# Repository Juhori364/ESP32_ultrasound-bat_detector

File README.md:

# ESP32_ultrasound-bat_detector

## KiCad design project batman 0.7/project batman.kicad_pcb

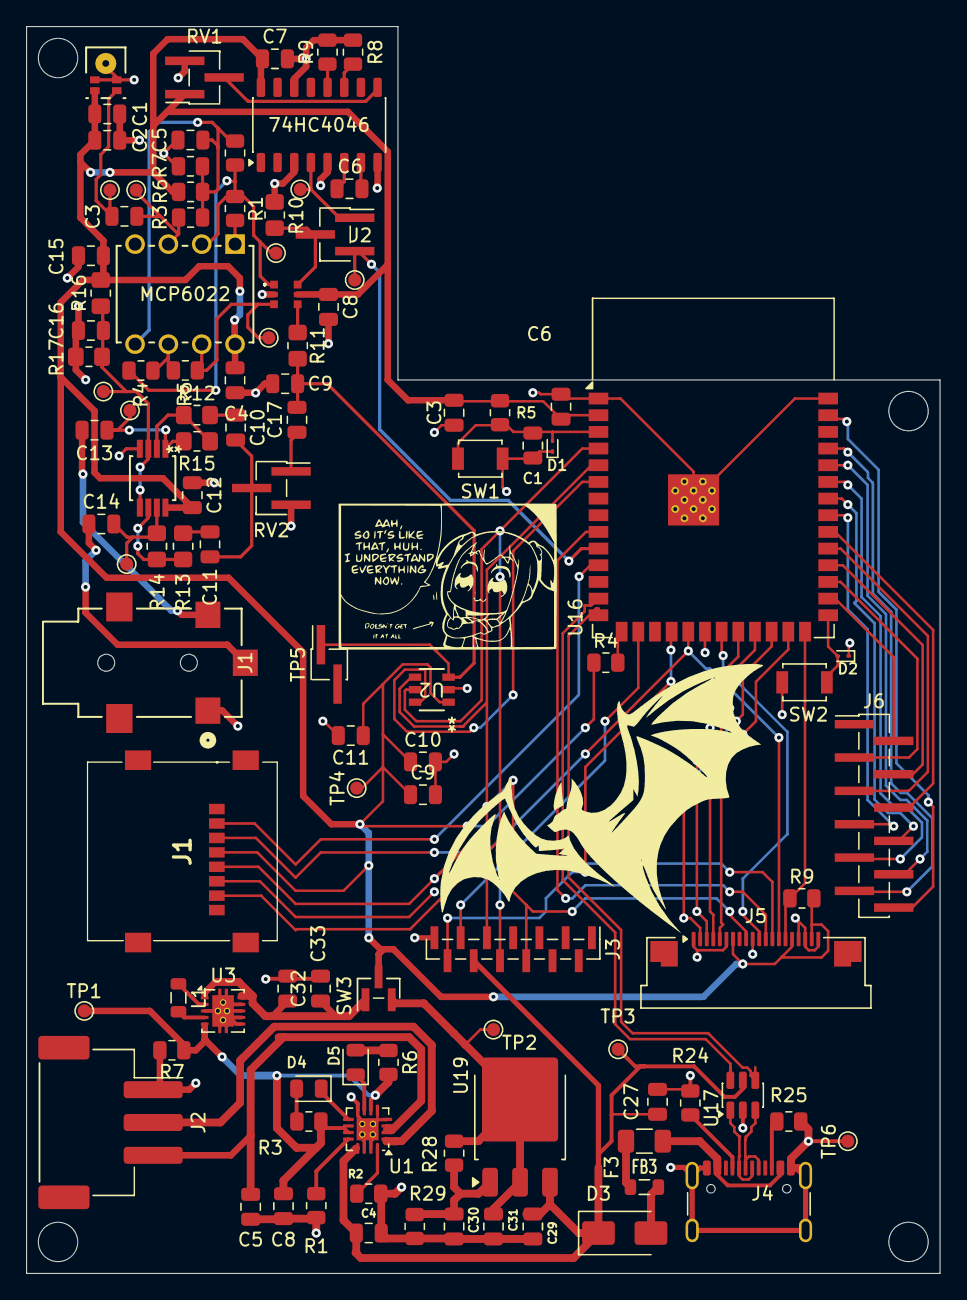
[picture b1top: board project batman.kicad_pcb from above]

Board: 2 copper layers, 69.6 x 95.0 mm, 109 parts (0 on the bottom side), 82 nets.

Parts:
74HC4046: 4046; JEITA_SOIC-16_3.9x9.9mm_P1.27mm
74LVC1G3156GW1: 74LVC1G3157GW125
C1: 1u; C_0805_2012Metric
C1#2, C15, C16, C17: 1uF; C_0805_2012Metric
C2: 1000pF; C_0805_2012Metric
C3: 150pF; C_0805_2012Metric
C3#2, C27: 100n; C_0805_2012Metric
C4, C7, C8, C9#2, C12: 100nF; C_0805_2012Metric
C4#2: 1µF; C_0805_2012Metric
C5, C29, C30: 10uF; C_0805_2012Metric
C5#2, C8#2, C9, C10#2, C11: 4.7µF; C_0805_2012Metric
C6: 0; C_0805_2012Metric
C6#2: 10u; C_0805_2012Metric
C10, C11#2: 2.2uF; C_0805_2012Metric
C13, C14: 220uF; C_0805_2012Metric
C31, C32, C33: 100uF; C_0805_2012Metric
D1, D2: ESD9B3.3ST5G; D_SOD-923
D3: B140-E3; D_SMA
D4, D5: LED; LED_0805_2012Metric
F3: 1A; Fuse_1206_3216Metric
FB3: BLM21PG220; L_0805_2012Metric
G: LOGO
IMP23ABSU1: RHLGA5_3P5X2P65X0P98_STM
J1: MEM2067-02-180-00-A; MEM20670218000A
J1#2: AudioJack2_Ground; JACK_1503 03_LMB
J2: Conn_01x03; JST_XH_S3B-XH-SM4-TB_1x03-1MP_P2.50mm_Horizontal
J2#2: Conn_01x03_Pin; PinHeader_1x03_P1.27mm_Vertical_SMD_Pin1Right
J3: Conn_01x13_Pin; PinHeader_1x13_P1.00mm_Vertical_SMD_Pin1Left
J4: USB_C_Receptacle_USB2.0_16P; USB_C_Receptacle_GCT_USB4105-xx-A_16P_TopMnt_Horizontal
J5: Conn_01x20_Pin; Amphenol_F32Q-1A7x1-11020_1x20-1MP_P0.5mm_Horizontal
J6: Conn_01x12_Pin; PinHeader_1x12_P1.27mm_Vertical_SMD_Pin1Left
L1: 2.2µH; L_0805_2012Metric
MCP6022: PDIP8_300MC_MCH
R1: 4.32k; R_0805_2012Metric
R1#2, R7: 100k; R_0805_2012Metric
R2: 2.94k; R_0805_2012Metric
R2#2, R4, R4#2, R5, R5#2, R6#2, R7#2, R9: 10k; R_0805_2012Metric
R3: 50k; R_0805_2012Metric
R3#2, R6: 1k; R_0805_2012Metric
R8, R9#2: 0; R_0805_2012Metric
R10, R16, R17: 100k; R_0805_2012Metric_Pad1.20x1.40mm_HandSolder
R11: 330; R_0805_2012Metric_Pad1.20x1.40mm_HandSolder
R12, R13: 3.9k; R_0805_2012Metric_Pad1.20x1.40mm_HandSolder
R14, R15: 39k; R_0805_2012Metric_Pad1.20x1.40mm_HandSolder
R24, R25: 5.1k; R_0805_2012Metric
R28: 610; R_0805_2012Metric
R29: 1000; R_0805_2012Metric
RV1, RV2: POT; PinHeader_1x03_P1.27mm_Vertical_SMD_Pin1Right
SW1: RESET; SW_SPST_B3U-1000P
SW2: BOOT; SW_SPST_B3U-1000P
SW3: SW_Nidec_CAS-120A1; PinHeader_1x03_P1.00mm_Vertical_SMD_Pin1Left
TP1, TP1#2, TP2, TP2#2, TP3, TP4, TP4#2, TP5#2, TP6, TP7, TP8, TP9, TP10, TP11: TestPoint; TestPoint_Pad_D1.0mm
TP5: TestPoint; PinHeader_1x02_P1.27mm_Vertical_SMD_Pin1Right
TS482IST1: MINISO8_3P1X3P2X0P65_STM
U1: BQ24230RGT; VQFN-16-1EP_3x3mm_P0.5mm_EP1.68x1.68mm_ThermalVias
U2: AD7276AUJZ-500RL7; UJ_6_ADI
U3: TPS63001; Texas_DRC0010J_ThermalVias
U16: ESP32-S3-WROOM-1
U17: USBLC6-2SC6; SOT-23-6
U19: LM1117DT-ADJ; TO-252-3_TabPin2

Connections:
+3.3V: 74HC4046.16 (VDD), 74LVC1G3156GW1.5 (Vcc), C1#2.2, C2.2, C3#2.1, C4.2, C6#2.1, C7.1, C8.1, C9.1, C10#2.1, C11.1, C12.2, C15.1, IMP23ABSU1.5 (Vin), J1.P4 (VDD), J5.7, J5.16, J5.19, MCP6022.8 (Vdd), R4.1, R5#2.1, R6#2.2, R9.2, R16.2, RV1.1, SW3.2 (B), TP4#2.1 (1_1), TS482IST1.8 (VCC), U2.1 (VDD), U16.2 (3V3)
+5V: C4#2.1, C27.1, C29.1, D3.1 (K), J3.10, TP3.1 (1_1), U1.13 (IN), U17.5 (VBUS), U19.3 (VI)
/ADC_CS: U2.6 (CS*), U16.6 (IO6)
/D+: J4.A6 (D+), J4.B6 (D+), U17.3 (I/O2)
/D-: J4.A7 (D-), J4.B7 (D-), U17.1 (I/O1)
/DP2_CS: J5.12, U16.9 (IO16)
/DP_CS: J3.12, U16.18 (IO10)
/DP_RESET: J3.11, U16.16 (IO46)
/DP_RESET2: J5.15, R9.1, U16.26 (IO45)
/DP_cmd_select: J5.11, U16.21 (IO13)
/EN: C1.1, D1.2 (A2), R5#2.2, SW1.2 (B), U16.3 (EN)
/ESP LO: J2#2.3, TP10.1 (1_1), U16.10 (IO17)
/GPIO22: J5.5, U16.22 (IO14)
/GPIO23: J5.4, U16.23 (IO21)
/GPIO24: J5.3, U16.24 (IO47)
/GPIO25: J5.2, U16.25 (IO48)
/GPIO28: J6.2, U16.28 (IO35)
/GPIO29: J6.3, U16.29 (IO36)
/GPIO30: J6.4, U16.30 (IO37)
/GPIO31: J6.5, U16.31 (IO38)
/GPIO32: J6.6, U16.32 (IO39)
/GPIO33: J6.7, U16.33 (IO40)
/GPIO34: J6.8, U16.34 (IO41)
/GPIO35: J6.9, U16.35 (IO42)
/GPIO36: J6.10, U16.36 (RXD0)
/GPIO37: J6.11, U16.37 (TXD0)
/GPIO39: J6.12, U16.39 (IO1)
/IO0: D2.2 (A2), SW2.2 (B), U16.27 (IO0)
/Left: C13.1, J1#2.3 (R)
/MISO: J1.P7 (DAT0), J3.6, J5.9, U2.5 (SDATA), U16.4 (IO4)
/MOSI: J1.P3 (CMD), J3.9, J5.14, U16.19 (IO11)
/PW_switch_1: C32.1, C33.1, SW3.1 (C), U3.1 (VOUT), U3.10 (FB)
/PW_switch_2: C31.1, R28.1, SW3.3 (A), TP2.1 (1_1), U19.2 (VO)
/Right: C14.1, J1#2.2 (T)
/SCLK: J1.P5 (CLK), J3.8, J5.13, U2.4 (SCLK), U16.5 (IO5)
/USB_D+: U16.14 (USB_D+), U17.4 (I/O2)
/USB_D-: U16.13 (USB_D-), U17.6 (I/O1)
/bq_output: C8#2.2, R3#2.2, R6.2, R7.1, TP1#2.1 (1_1), U1.6 (EN1), U1.10 (OUT), U1.11 (OUT), U3.5 (VIN)
/sd_cs: J1.P2 (CD/DAT3), U16.11 (IO18)
/to ADC: C9#2.2, C17.2, R11.2, TP5.1 (1_1), U2.3 (VIN)
GND: 74HC4046.3 (RefIn), 74HC4046.5 (Inh), 74HC4046.8 (VSS), 74HC4046.14 (SigIn), 74LVC1G3156GW1.2 (GND), C1.2, C1#2.1, C2.1, C3#2.2, C4.1, C4#2.2, C5.1, C5#2.2, C6#2.2, C7.2, C8.2, C8#2.1, C9.2, C9#2.1, C10#2.2, C11.2, C12.1, C15.2, C16.2, C27.2, C29.2, C30.2, C31.2, C32.2, C33.2, D1.1 (A1), D2.1 (A1), IMP23ABSU1.2 (GND), IMP23ABSU1.3, IMP23ABSU1.4 (GND), J1.P6 (VSS), J1#2.1 (G), J2.1, J3.13, J4.A1 (GND), J4.A12 (GND), J4.B1 (GND), J4.B12 (GND), J4.S1 (SHIELD), J5.1, J5.6, J5.10, J5.17, J5.18, J5.20, MCP6022.4 (Vss), R1.1, R2.1, R7.2, R7#2.1, R8.1, R9#2.1, R10.2, R17.1, R24.2, R25.2, R29.2, RV1.3, RV2.3, SW1.1 (A), SW2.1 (A), TP6.1 (1_1), TS482IST1.4 (GND), U1.4 (CE), U1.5 (EN2), U1.8 (VSS), U1.14 (TMR), U1.15 (TD), U1.17 (VSS), U2.2 (GND), U3.3 (PGND), U3.6 (EN), U3.7 (PS/SYNC), U3.8 (VINA), U3.9 (GND), U3.11 (PGND), U16.1 (GND), U16.20 (IO12), U16.40 (GND), U16.41 (GND), U17.2 (GND)
unnamed: 74HC4046.6 (C1), C6.2
unnamed: 74HC4046.7 (C2), C6.1
unnamed: 74HC4046.4 (FOUT), J2#2.1, TP11.1 (1_1)
unnamed: 74HC4046.11 (R1), R8.2
unnamed: 74HC4046.12 (R2), R9#2.2
unnamed: 74HC4046.9 (VCOin), RV1.2
unnamed: 74LVC1G3156GW1.6 (S), J2#2.2, R10.1
unnamed: 74LVC1G3156GW1.3 (Y0), MCP6022.7 (VoutB), R5.1, TP4.1 (1_1)
unnamed: 74LVC1G3156GW1.1 (Y1), MCP6022.2 (VinA-), R1#2.2, R2#2.1, R4#2.1, TP5#2.1 (1_1)
unnamed: 74LVC1G3156GW1.4 (Z), R11.1
unnamed: C10.1, R12.2
unnamed: C10.2, C11#2.2, RV2.2
unnamed: C11#2.1, R13.2
unnamed: C17.1, RV2.1
unnamed: D3.2 (A), FB3.2
unnamed: D4.2 (A), R3#2.1
unnamed: D4.1 (K), U1.9 (CHG)
unnamed: D5.2 (A), R6.1
unnamed: D5.1 (K), U1.7 (PGOOD)
unnamed: F3.1, J4.A4 (VBUS), J4.A9 (VBUS), J4.B4 (VBUS), J4.B9 (VBUS)
unnamed: F3.2, FB3.1
unnamed: C3.1, IMP23ABSU1.1 (Vout), TP1.1 (1_1)
unnamed: J2.2, U1.1 (TS)
unnamed: C5#2.1, J2.3, U1.2 (BAT), U1.3 (BAT)
unnamed: J4.A5 (CC1), R24.1
unnamed: J4.B5 (CC2), R25.1
unnamed: C3.2, MCP6022.3 (VinA+), R3.1, TP2#2.1 (1_1)
unnamed: C5.2, MCP6022.5 (VinB+), R2#2.2, R3.2, R6#2.1, R7#2.2
unnamed: MCP6022.6 (VinB-), R4#2.2, R5.2
unnamed: MCP6022.1 (VoutA), R1#2.1
unnamed: C13.2, R15.1, TP9.1 (1_1), TS482IST1.1 (OUT(1))
unnamed: C14.2, R14.1, TP8.1 (1_1), TS482IST1.7 (OUT(2))
unnamed: C16.1, R16.1, R17.2, TP7.1 (1_1), TS482IST1.3 (Vin+(1)), TS482IST1.5 (Vin+(2))
unnamed: R12.1, R15.2, TS482IST1.2 (Vin-(1))
unnamed: R13.1, R14.2, TS482IST1.6 (Vin-(2))
unnamed: R1.2, U1.12 (ILIM)
unnamed: R2.2, U1.16 (ISET)
unnamed: L1.2, U3.4 (L1)
unnamed: L1.1, U3.2 (L2)
unnamed: R4.2, U16.15 (IO3)
unnamed: C30.1, R28.2, R29.1, U19.1 (ADJ)
